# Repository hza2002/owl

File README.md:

# Owl
**Owl**, an acronym for **Orthogonal Wireless Layout**, combines the ergonomic freedom of wireless connectivity with a split keyboard design influenced by [Lily58](https://github.com/kata0510/Lily58), [Corne](https://github.com/foostan/crkbd), [Sofle](https://github.com/josefadamcik/SofleKeyboard) and [Torn](https://github.com/rtitmuss/torn) keyboards.

## Feature
- Owl uses **Pro Micro** Interconnect small controller board, which means easy for Maintenance and replacemen. And supports a variety of boards including [nice!nano](https://nicekeyboards.com/nice-nano) and [nrfmicro](https://github.com/joric/nrfmicro/) (I **have not tried yet**, but theoretically feasible).
- Low latency wireless, supported by [ZMK](https://github.com/zmkfirmware/zmk).
- Gorgeous **RGB** lighting effects.
- Two multifunctional **OLED** screens that can display keyboard battery level and connection status.
- Split keyboard conforms to **ergonomics**.
- A total of two PCBs compatible with Cherry MX switches, Kailh choc Low Profile switches, and Gateron Low Profile switches.
- **Double-sided** PCB design, both sides are universal.
## Building your own
Detailed [Build Guide](https://nand.fun/en/series/owl-split-keyboard/).

Please make sure you can get the ability to build the keyboard:
- Soldering circuit components
- Circuit board production
- 3D printing
- Using GitHub action to build firmware
- Consulting documents carefully
## License

The Owl Keyboard is licensed under [Creative Commons Attribution-NonCommercial 4.0 International License](https://creativecommons.org/licenses/by-nc/4.0).

This PCB design may be freely reproduced, modified, and manufactured for personal use only. If you would like to use this design commercially please contact me at hza2002@foxmail.com to request permission.
## Thanks
I would like to express my sincere gratitude to the creators and contributors of various articles, repositories, and tutorials that greatly contributed to the development of the 'Owl' keyboard. 

These resources provided me with essential insights and knowledge throughout the development process. I am truly thankful for the open-source community's generosity and collaborative spirit."

Without their invaluable resources, this project would not have been possible. I encourage anyone interested in the details of this project to explore the following sources:
### PCB
- [Use KiCad to make PCB - zero-based KiCad Chinese tutorial](https://haipeng.me/2017/03/01/kicad-tutorial/)
- [Kicad advanced tutorial 1: new component](https://haipeng.me/2018/05/24/kicad_advanced_tutorial_1_new_component/)
- [Kicad advanced tutorial 2: new logo](https://haipeng.me/2018/07/11/kicad_advanced_tutorial_2_new_logo/)
- [Kicad advanced tutorial 3: mask opening](https://haipeng.me/2019/09/02/kicad-mask-opening/)
- [How to generate Gerber and Drill files in KiCad 7](https://jlcpcb.com/help/article/362-how-to-generate-gerber-and-drill-files-in-kicad-7)
- [How to generate the BOM and Centroid file from KiCAD](https://jlcpcb.com/help/article/81-How-to-generate-the-BOM-and-Centroid-file-from-KiCAD)
### Other Keyboard
I took inspiration from other keyboards I'd used or liked:
- [Torn](https://github.com/rtitmuss/torn) My first DIY keyboard, easy to build and robust to use. The reason of the Owl keyboard layout (basicly the same).
- [Corne](https://github.com/foostan/crkbd) Handsome and technological design, various styles of PCB provide important reference.
- [Sofle](https://github.com/josefadamcik/SofleKeyboard) Referenced some circuit design and component selection.
- [Lily58](https://github.com/kata0510/Lily58) Referenced some circuit design and component selection.
### helpful repo
- [key-switches.pretty](https://github.com/siderakb/key-switches.pretty) Very helpful. It contains various keyboard footprints and has exquisite instruction tables.
- [keyswitches.pretty](https://github.com/daprice/keyswitches.pretty) KiCAD footprint library for kailh choc and MX-style mechanical switches and their associated sockets.
- [Keebio-Parts.pretty](https://github.com/keebio/Keebio-Parts.pretty) Various KiCAD footprints for mechanical keyboard parts.
## Gallery

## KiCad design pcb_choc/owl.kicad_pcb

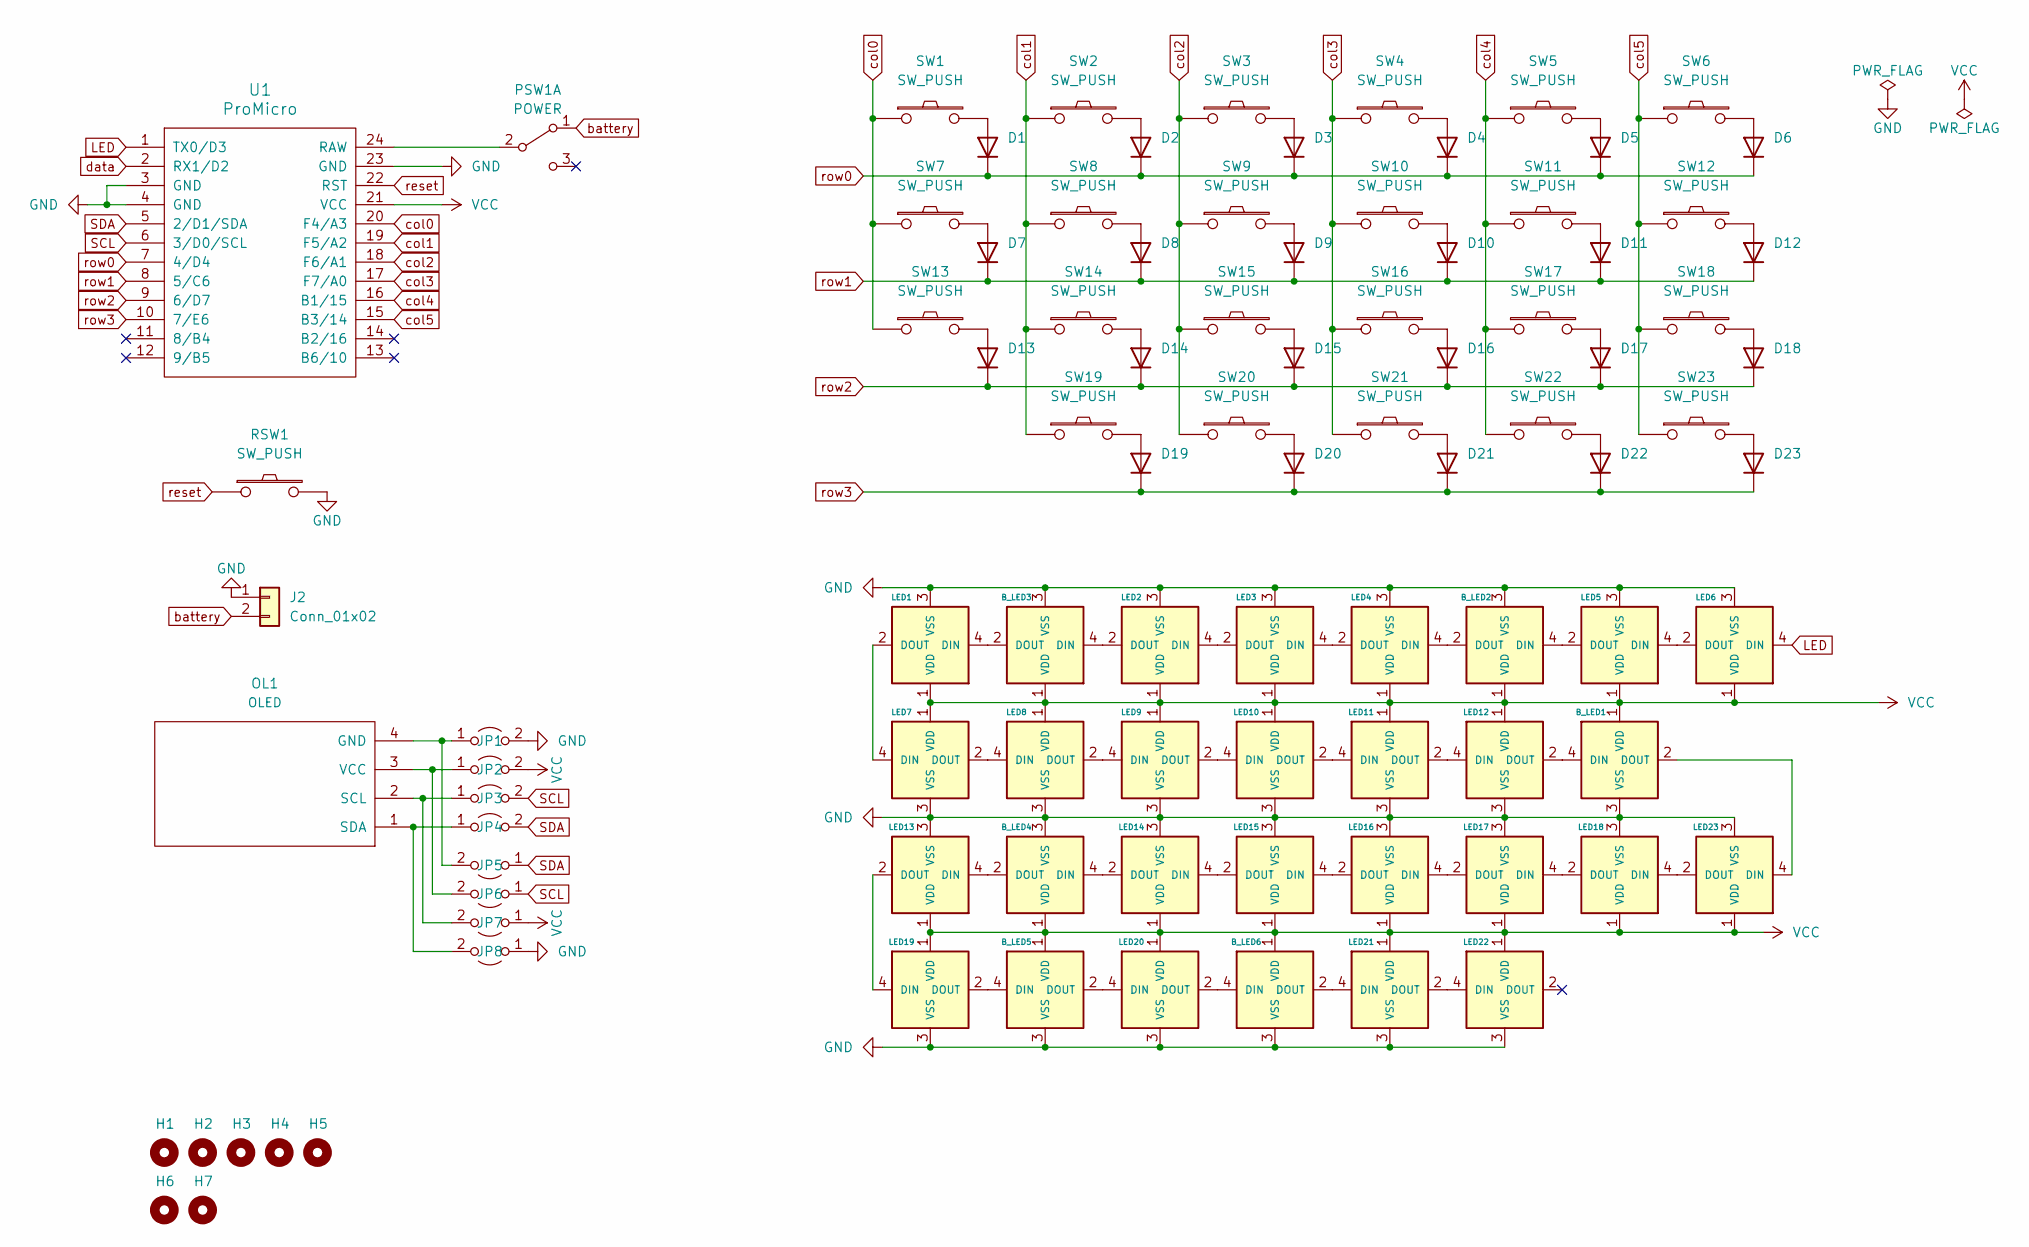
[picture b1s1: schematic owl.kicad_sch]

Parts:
B_LED1, B_LED2, B_LED3, B_LED4, B_LED5, B_LED6: YS-SK6812MINI-E; YS-SK6812MINI-E_Back_Rev
D1, D2, D3, D4, D5, D6, D7, D8, D9, D10, D11, D12, D13, D14, D15, D16, D17, D18, D19, D20, D21, D22, D23: D; Diode_TH_SMD_Rev
H1, H2, H3, H4, H5, H6, H7: MountingHole; M2_Hole_TH
J2: Conn_01x02; JST_PH_S2B-PH-SM4-TB_1x02-1MP_P2.00mm_Horizontal
JP1, JP2, JP3, JP4, JP5, JP6, JP7, JP8: Jumper_2_Open; Jumper
LED1, LED2, LED3, LED4, LED5, LED6, LED7, LED8, LED9, LED10, LED11, LED12, LED13, LED14, LED15, LED16, LED17, LED18, LED19, LED20, LED21, LED22, LED23: YS-SK6812MINI-E; YS-SK6812MINI-E_Rev
OL1: OLED; OLED_4Pin_Rev
PSW1: POWER; SW_SPDT_PCM12_Rev
RSW1: SW_PUSH; SW_Tactile_SPST_Angled_PTS645Vx39-2LFS_Rev
SW1, SW2, SW3, SW4, SW5, SW6, SW7, SW8, SW9, SW10, SW11, SW12, SW13, SW14, SW15, SW16, SW17, SW18, SW19, SW20, SW21, SW22, SW23: SW_PUSH; SW_MX_Choc_HotSwap_double
U1: ProMicro; ProMicro_Rev

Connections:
GND: B_LED1.3 (VSS), B_LED2.3 (VSS), B_LED3.3 (VSS), B_LED4.3 (VSS), B_LED5.3 (VSS), B_LED6.3 (VSS), JP1.2 (B), JP8.1 (A), LED1.3 (VSS), LED2.3 (VSS), LED3.3 (VSS), LED4.3 (VSS), LED5.3 (VSS), LED6.3 (VSS), LED7.3 (VSS), LED8.3 (VSS), LED9.3 (VSS), LED10.3 (VSS), LED11.3 (VSS), LED12.3 (VSS), LED13.3 (VSS), LED14.3 (VSS), LED15.3 (VSS), LED16.3 (VSS), LED17.3 (VSS), LED18.3 (VSS), LED19.3 (VSS), LED20.3 (VSS), LED21.3 (VSS), LED22.3 (VSS), LED23.3 (VSS), RSW1.2, U1.3 (GND), U1.4 (GND), U1.23 (GND); also elsewhere on the board
LED: LED6.4 (DIN), U1.1 (TX0/D3)
unnamed: B_LED1.4 (DIN), LED12.2 (DOUT)
unnamed: B_LED1.2 (DOUT), LED23.4 (DIN)
unnamed: B_LED2.4 (DIN), LED5.2 (DOUT)
unnamed: B_LED2.2 (DOUT), LED4.4 (DIN)
unnamed: B_LED3.4 (DIN), LED2.2 (DOUT)
unnamed: B_LED3.2 (DOUT), LED1.4 (DIN)
unnamed: B_LED4.4 (DIN), LED14.2 (DOUT)
unnamed: B_LED4.2 (DOUT), LED13.4 (DIN)
unnamed: B_LED5.4 (DIN), LED19.2 (DOUT)
unnamed: B_LED5.2 (DOUT), LED20.4 (DIN)
unnamed: B_LED6.4 (DIN), LED20.2 (DOUT)
unnamed: B_LED6.2 (DOUT), LED21.4 (DIN)
unnamed: D1.2 (A), SW1.2
unnamed: D2.2 (A), SW2.2
unnamed: D3.2 (A), SW3.2
unnamed: D4.2 (A), SW4.2
unnamed: D5.2 (A), SW5.2
unnamed: D6.2 (A), SW6.2
unnamed: D7.2 (A), SW7.2
unnamed: D8.2 (A), SW8.2
unnamed: D9.2 (A), SW9.2
unnamed: D10.2 (A), SW10.2
unnamed: D11.2 (A), SW11.2
unnamed: D12.2 (A), SW12.2
unnamed: D13.2 (A), SW13.2
unnamed: D14.2 (A), SW14.2
unnamed: D15.2 (A), SW15.2
unnamed: D16.2 (A), SW16.2
unnamed: D17.2 (A), SW17.2
unnamed: D18.2 (A), SW18.2
unnamed: D19.2 (A), SW19.2
unnamed: D20.2 (A), SW20.2
unnamed: D21.2 (A), SW21.2
unnamed: D22.2 (A), SW22.2
unnamed: D23.2 (A), SW23.2
unnamed: JP1.1 (A), JP5.2 (B), OL1.4 (GND)
unnamed: JP2.1 (A), JP6.2 (B), OL1.3 (VCC)
unnamed: JP3.1 (A), JP7.2 (B), OL1.2 (SCL)
unnamed: JP4.1 (A), JP8.2 (B), OL1.1 (SDA)
unnamed: LED1.2 (DOUT), LED7.4 (DIN)
unnamed: LED2.4 (DIN), LED3.2 (DOUT)
unnamed: LED3.4 (DIN), LED4.2 (DOUT)
unnamed: LED5.4 (DIN), LED6.2 (DOUT)
unnamed: LED7.2 (DOUT), LED8.4 (DIN)
unnamed: LED8.2 (DOUT), LED9.4 (DIN)
unnamed: LED9.2 (DOUT), LED10.4 (DIN)
unnamed: LED10.2 (DOUT), LED11.4 (DIN)
unnamed: LED11.2 (DOUT), LED12.4 (DIN)
unnamed: LED13.2 (DOUT), LED19.4 (DIN)
unnamed: LED14.4 (DIN), LED15.2 (DOUT)
unnamed: LED15.4 (DIN), LED16.2 (DOUT)
unnamed: LED16.4 (DIN), LED17.2 (DOUT)
unnamed: LED17.4 (DIN), LED18.2 (DOUT)
unnamed: LED18.4 (DIN), LED23.2 (DOUT)
unnamed: LED21.2 (DOUT), LED22.4 (DIN)
unnamed: PSW1.2 (B), U1.24 (RAW)
SCL: JP3.2 (B), JP6.1 (A), U1.6 (3/D0/SCL)
SDA: JP4.2 (B), JP5.1 (A), U1.5 (2/D1/SDA)
VCC: B_LED1.1 (VDD), B_LED2.1 (VDD), B_LED3.1 (VDD), B_LED4.1 (VDD), B_LED5.1 (VDD), B_LED6.1 (VDD), JP2.2 (B), JP7.1 (A), LED1.1 (VDD), LED2.1 (VDD), LED3.1 (VDD), LED4.1 (VDD), LED5.1 (VDD), LED6.1 (VDD), LED7.1 (VDD), LED8.1 (VDD), LED9.1 (VDD), LED10.1 (VDD), LED11.1 (VDD), LED12.1 (VDD), LED13.1 (VDD), LED14.1 (VDD), LED15.1 (VDD), LED16.1 (VDD), LED17.1 (VDD), LED18.1 (VDD), LED19.1 (VDD), LED20.1 (VDD), LED21.1 (VDD), LED22.1 (VDD), LED23.1 (VDD), U1.21 (VCC)
battery: PSW1.1 (A); also elsewhere on the board
col0: SW1.1, SW7.1, SW13.1, U1.20 (F4/A3)
col1: SW2.1, SW8.1, SW14.1, SW19.1, U1.19 (F5/A2)
col2: SW3.1, SW9.1, SW15.1, SW20.1, U1.18 (F6/A1)
col3: SW4.1, SW10.1, SW16.1, SW21.1, U1.17 (F7/A0)
col4: SW5.1, SW11.1, SW17.1, SW22.1, U1.16 (B1/15)
col5: SW6.1, SW12.1, SW18.1, SW23.1, U1.15 (B3/14)
data: U1.2 (RX1/D2)
reset: RSW1.1, U1.22 (RST)
row0: D1.1 (K), D2.1 (K), D3.1 (K), D4.1 (K), D5.1 (K), D6.1 (K), U1.7 (4/D4)
row1: D7.1 (K), D8.1 (K), D9.1 (K), D10.1 (K), D11.1 (K), D12.1 (K), U1.8 (5/C6)
row2: D13.1 (K), D14.1 (K), D15.1 (K), D16.1 (K), D17.1 (K), D18.1 (K), U1.9 (6/D7)
row3: D19.1 (K), D20.1 (K), D21.1 (K), D22.1 (K), D23.1 (K), U1.10 (7/E6)

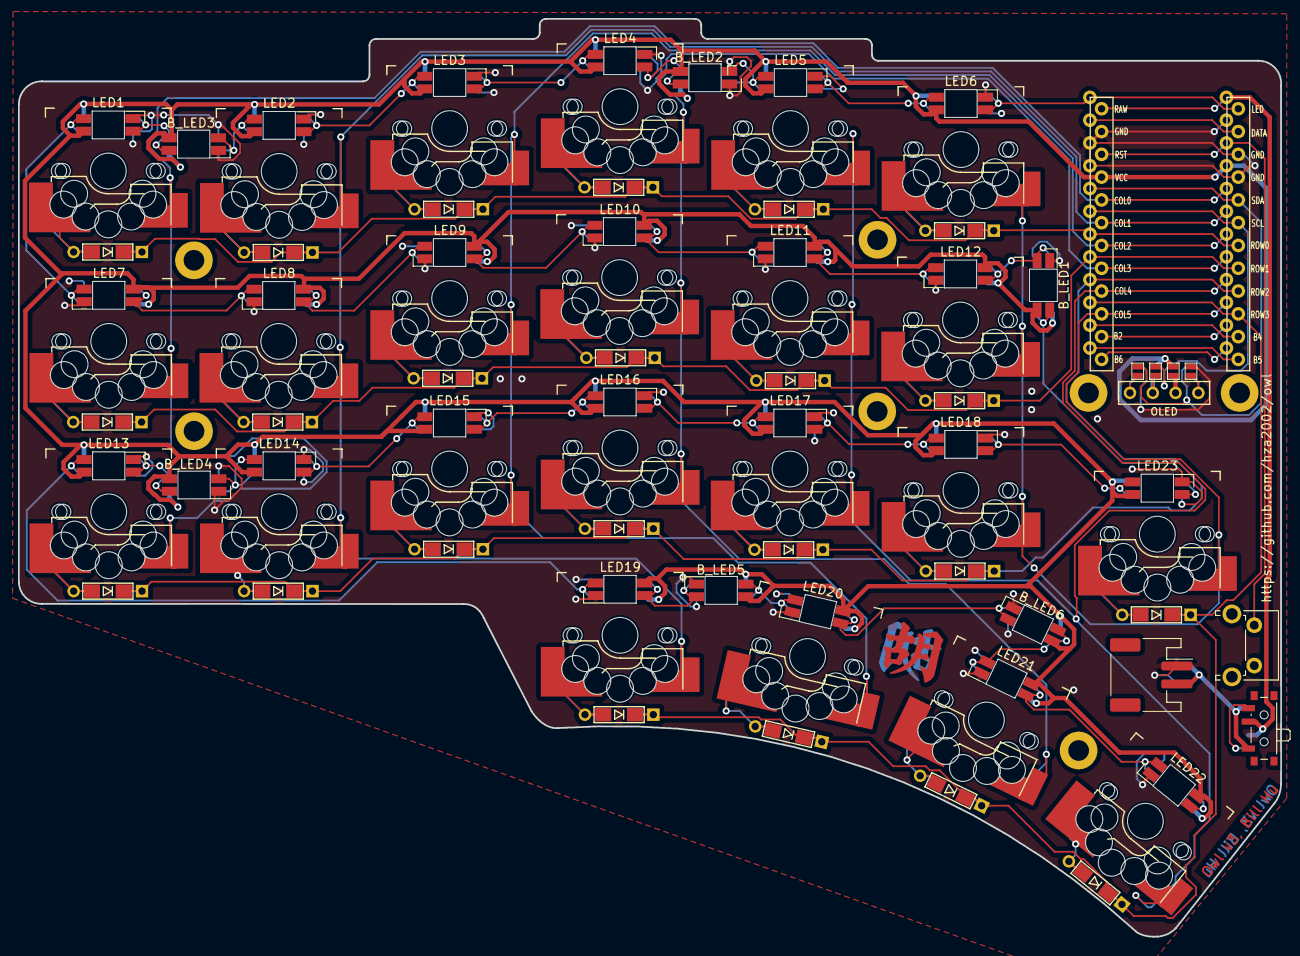
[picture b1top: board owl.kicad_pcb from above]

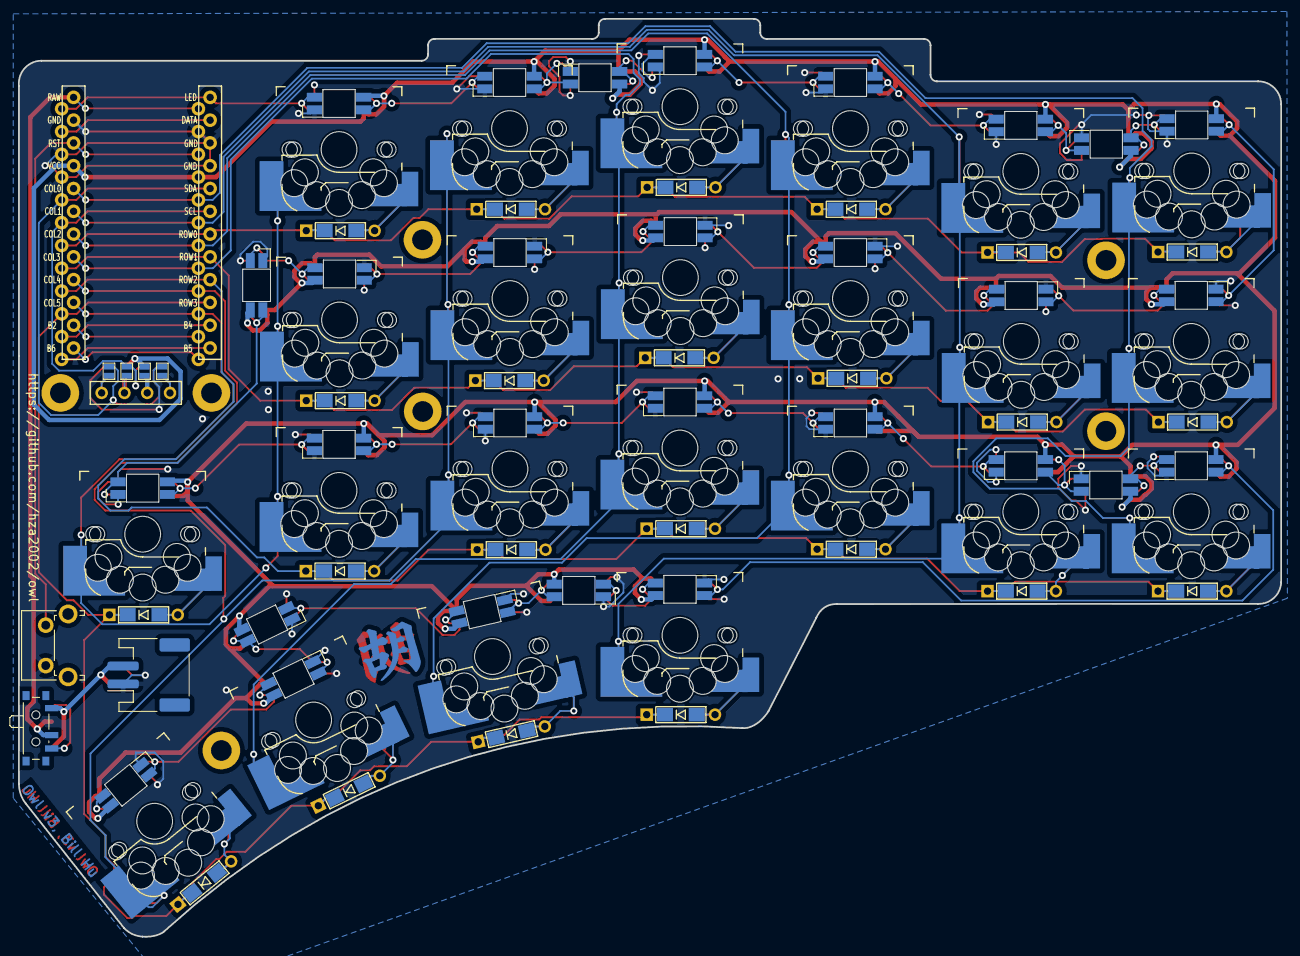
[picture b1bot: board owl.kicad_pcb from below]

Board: 2 copper layers, 140.7 x 102.3 mm, 97 parts (6 on the bottom side), 73 nets.

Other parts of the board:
J1: Conn_01x02; JST_PH_S2B-PH-SM4-TB_1x02-1MP_P2.00mm_Horizontal
logo: LOGO; owl_logo
logo#2: LOGO; owl_logo

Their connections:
GND: J1.1; also elsewhere on the board
battery: J1.2; also elsewhere on the board

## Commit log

2024-03-09 Add pcb and case
2024-03-09 Change to Creative Commons Public Licenses
2024-03-10 Add README doc
2024-03-11 Add build guide
2024-03-11 Repair build guide picture error
2024-03-15 Complete doc except 3D-printed case and chip install
2024-03-18 Finish chip install tutorial
    Add chip install tutorial
2024-03-18 Finish 3D-printed case install tutorial
2024-04-06 Update project acronym
2024-08-13 Combine readme gallery into one picture
2024-10-19 Initial repo
    Use Creative Commons Public Licenses
    Add gitignore
2024-10-19 Add pcb file
2024-10-19 Add README doc
    Update project acronym
    Add build guide
    Combine readme gallery into one picture
    Move build guide to website and use compressed images
2024-10-19 Add cases
